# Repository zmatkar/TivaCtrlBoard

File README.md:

# TivaCtrlBoard
TivaCtrlBoard hardware sources. 

It is based on TM4C123G6H microcontroller. This board is not designed specifically
for any project - main purpose is to be universal control board with monochromatic LCD display (optionally OLED),
RGB LED and rotary encoder which fits into small aluminium case - https://www.aliexpress.com/item/1005001699595657.html

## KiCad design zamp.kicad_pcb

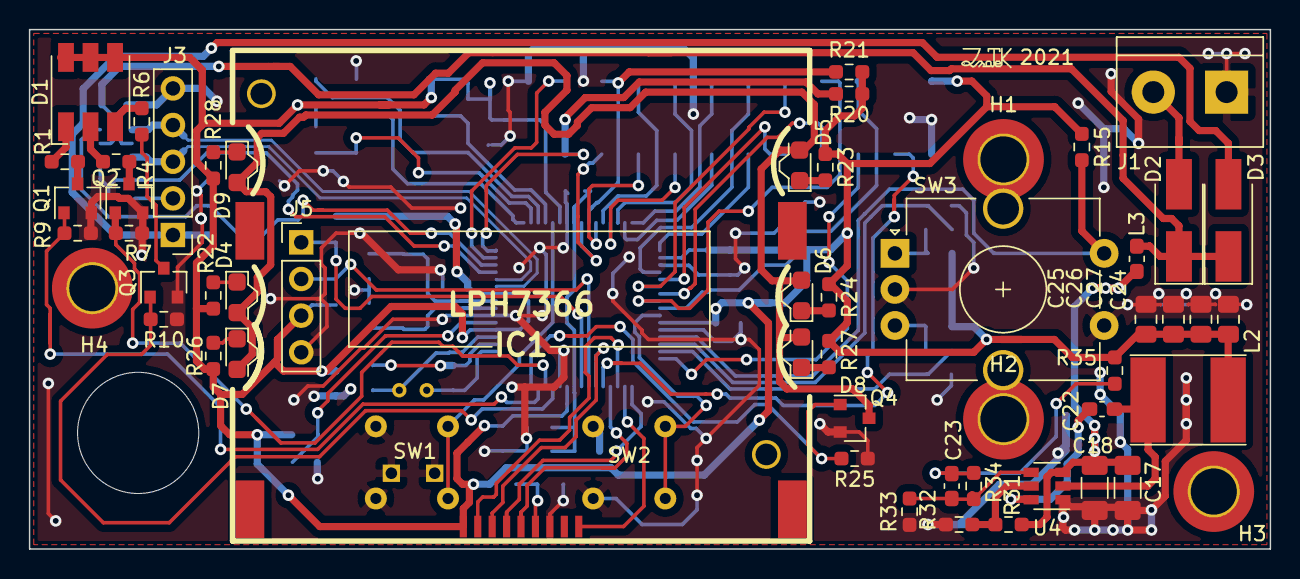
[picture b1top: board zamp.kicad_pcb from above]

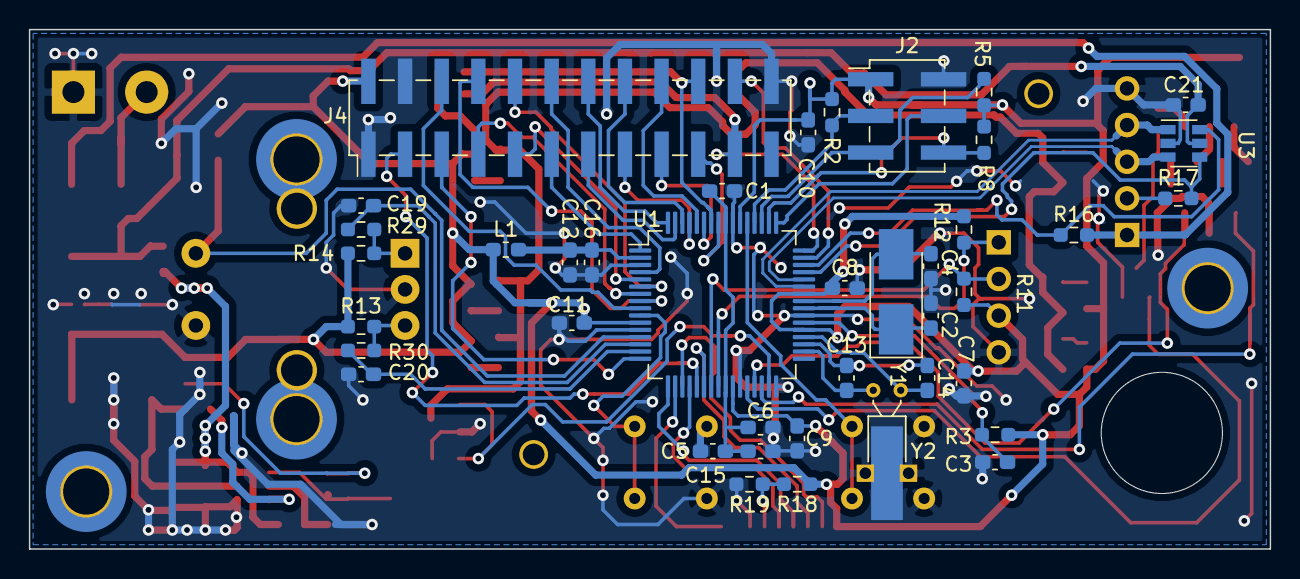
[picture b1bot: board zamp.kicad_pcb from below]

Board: 2 copper layers, 86.0 x 36.0 mm, 96 parts (40 on the bottom side), 79 nets.

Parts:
C1, C7: 2u2; C_0603_1608Metric_Pad1.08x0.95mm_HandSolder
C2, C4, C13, C14, C19, C20: 22p; C_0603_1608Metric_Pad1.08x0.95mm_HandSolder
C3, C5, C8, C9, C10, C11, C15, C21, C22: 100n; C_0603_1608Metric_Pad1.08x0.95mm_HandSolder
C6, C12: 1u; C_0603_1608Metric_Pad1.08x0.95mm_HandSolder
C16: 10n; C_0603_1608Metric_Pad1.08x0.95mm_HandSolder
C17: 100n/30V; C_1206_3216Metric_Pad1.33x1.80mm_HandSolder
C18: 10u/30V; C_1206_3216Metric_Pad1.33x1.80mm_HandSolder
C23: 100p; C_0603_1608Metric_Pad1.08x0.95mm_HandSolder
C24, C25, C26, C27: 10u; C_0805_2012Metric_Pad1.18x1.45mm_HandSolder
D1: LED_RGB; LED_RGB_5050-6
D2, D3: D_Schottky; D_SMA_Handsoldering
D4, D5, D6, D7, D8, D9: LED; LED_0603_90rotated
H1, H2, H3, H4: MountingHole; MountingHole_3.2mm_M3_DIN965_Pad_TopBottom
IC1: LPH7366
J1: Screw_Terminal_01x02; TerminalBlock_bornier-2_P5.08mm
J2: Conn_02x03_Odd_Even; PinHeader_2x03_P2.54mm_Vertical_SMD
J3: Conn_01x04; PinHeader_1x05_P2.54mm_Vertical
J4: Conn_02x10_Odd_Even; PinHeader_2x12_P2.54mm_Vertical_SMD
J5: Conn_01x04; PinHeader_1x04_P2.54mm_Vertical
L1, L3: 10u; L_0603_1608Metric_Pad1.05x0.95mm_HandSolder
L2: 10u; L_Taiyo-Yuden_NR-60xx_HandSoldering
Q1, Q2, Q3, Q4: BSN20; SOT-23
R1, R4, R6: 330; R_0603_1608Metric_Pad0.98x0.95mm_HandSolder
R2, R5, R8: 1k; R_0603_1608Metric_Pad0.98x0.95mm_HandSolder
R3, R13, R14, R29, R30: 10k; R_0603_1608Metric_Pad0.98x0.95mm_HandSolder
R7, R9, R10, R18, R19, R25, R34: 100k; R_0603_1608Metric_Pad0.98x0.95mm_HandSolder
R11, R12, R20, R21: 4k7; R_0603_1608Metric_Pad0.98x0.95mm_HandSolder
R15: R; R_0603_1608Metric_Pad0.98x0.95mm_HandSolder
R16, R17, R22, R23, R24, R26, R27, R28: 220; R_0603_1608Metric_Pad0.98x0.95mm_HandSolder
R31, R32: 1M; R_0603_1608Metric_Pad0.98x0.95mm_HandSolder
R33: 22k; R_0603_1608Metric_Pad0.98x0.95mm_HandSolder
R35: 47; R_0603_1608Metric_Pad0.98x0.95mm_HandSolder
SW1, SW2: SW_SPST; BTN_9mm_pitch5x5mm
SW3: Rotary_Encoder_Switch; RotaryEncoder_Alps_EC12E-Switch_Vertical_H20mm_CircularMoun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
U1: TM4C123GH6PM; LQFP-64_10x10mm_P0.5mm
U3: SRV05-4; SOT-23-6
U4: TPS54202DDC; SOT-23-6
Y1: 16MHz; Crystal_SMD_5032-2Pin_5.0x3.2mm_HandSoldering
Y2: 32.768k; Crystal_C26-LF_D2.1mm_L6.5mm_Horizontal_1EP_style2

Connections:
+3V3: C7.1, C8.1, C9.1, C10.1, C11.1, C24.2, C25.2, C26.2, C27.2, D1.4, D1.5, D1.6, IC1.1, J2.1, J4.2, J5.3, L1.1, L2.2, R2.1, R3.2, R5.1, R8.1, R11.1, R12.1, R13.1, R14.1, R15.1, R18.2, R20.1, R21.1, R22.1, R23.1, R24.1, R26.1, R27.1, R28.1, R35.1, U1.11, U1.26, U1.37, U1.42, U1.54
/DISP_BL: Q4.1, R25.2, U1.31
/D_C: IC1.4, U1.17
/IOAIN0: J4.10, U1.6
/IOAIN1: J4.7, U1.7
/IOAIN2: J4.8, U1.8
/IOAIN3: J4.6, U1.9
/IOAIN8: J4.18, U1.60
/IOAIN9: J4.17, U1.59
/IOMISO: J4.11, U1.1
/IOMOSI: J4.12, U1.4
/IOPA4: J4.3, U1.21
/IOPC4: J4.5, U1.16
/IOPD0: J4.15, U1.61
/IOPD1: J4.16, U1.62
/IOPD2: J4.13, U1.63
/IOPD3: J4.14, U1.64
/IOPF4: J4.9, U1.5
/IOSCL: J4.22, U1.47
/IOSCLK: J4.20, R21.2, U1.58
/IOSDA: J4.21, R20.2, U1.48
/IOnCS: J4.19, U1.57
/LEDB: Q3.1, R10.2, U1.28
/LEDG: Q2.1, R7.2, U1.29
/LEDR: Q1.1, R9.2, U1.30
/PC5: C20.1, R30.2, U1.15
/PC6: C19.1, R29.2, U1.14
/PC7: R15.2, SW3.S1, U1.13
/SCK: J5.2, R11.2, U1.23
/SCLK: IC1.2, U1.19
/SDA: J5.1, R12.2, U1.24
/SDIN: IC1.3, U1.22
/SW1: SW1.1, U1.53
/SW2: SW2.1, U1.10
/TCK: J2.3, R2.2, U1.52
/TDI: J2.6, R8.2, U1.50
/TDO: J2.4, U1.49
/TMS: J2.5, R5.2, U1.51
/USB0D+: J3.3, U1.44, U3.3
/USB0D-: J3.4, U1.43, U3.1
/USBID: R17.2, U1.45, U3.4
/USBVBUS: R16.1, U1.46, U3.6
/VDDA: C12.2, C16.2, L1.2, U1.2
/VDDC: C1.1, C5.1, C6.1, C15.1, U1.25, U1.56
/nCS: IC1.5, U1.20
/nRES: IC1.9, U1.18
GND: C1.2, C2.2, C3.2, C4.2, C5.2, C6.2, C7.2, C8.2, C9.2, C10.2, C11.2, C12.1, C15.2, C16.1, C17.2, C18.2, C19.2, C20.2, C21.2, C24.1, C25.1, C26.1, C27.1, IC1.7, J1.1, J2.2, J3.5, J4.1, J4.4, J4.24, J5.4, Q1.2, Q2.2, Q3.2, Q4.2, R7.1, R9.1, R10.1, R19.2, R25.1, R32.1, R33.1, SW1.2, SW2.2, SW3.C, SW3.S2, U1.3, U1.12, U1.27, U1.32, U1.39, U1.55, U3.2, U4.1, Y2.3
unnamed: C2.1, U1.40, Y1.1
unnamed: C3.1, R3.1, U1.38
unnamed: C4.1, U1.41, Y1.2
unnamed: C13.1, C14.2, U1.35
unnamed: C13.2, U1.34, Y2.1
unnamed: C14.1, U1.36, Y2.2
unnamed: C17.1, C18.1, L3.2, R31.1, U4.3
unnamed: C22.1, L2.1, U4.2
unnamed: C22.2, U4.6
unnamed: C23.1, R34.1, R35.2
unnamed: C23.2, R33.2, R34.2, U4.4
unnamed: D1.1, R1.1
unnamed: D1.2, R4.1
unnamed: D1.3, R6.1
unnamed: D2.2, J1.2
unnamed: D3.2, J3.1, R16.2
unnamed: D4.1, D5.1, D6.1, D7.1, D8.1, D9.1, Q4.3
unnamed: D4.2, R22.2
unnamed: D5.2, R23.2
unnamed: D6.2, R24.2
unnamed: D7.2, R26.2
unnamed: D8.2, R27.2
unnamed: D9.2, R28.2
unnamed: IC1.6, R18.1, R19.1
unnamed: J3.2, R17.1
unnamed: Q1.3, R1.2
unnamed: Q2.3, R4.2
unnamed: Q3.3, R6.2
unnamed: R13.2, R30.1, SW3.B
unnamed: R14.2, R29.1, SW3.A
unnamed: R31.2, R32.2, U4.5
VBUS: C21.1, D2.1, D3.1, L3.1, U3.5

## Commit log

2022-06-19 ZAMP hardware - initial commit
2022-06-19 Shematics in PDF
2022-06-19 Minor update
